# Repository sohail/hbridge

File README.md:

# H Bridge electronic circuit

H-Bridge is an electronic circuit that switches the polarity of voltage applied to a load.

Given the fact that by changing the direction of the rotation the DC motors can run with either polarity. An H bridge is an electronic circuit which can be used to switch the polarity of a attached motor, thus making the motor run forward or in backwards directions.

An H Bridge can be used in many different power electronics. The H Bridge of this repository which is built with few discrete components has one purpose only and that would be to control the direction of the rotation of a brushed DC motor.

### The list of components that you would need to make this circuit

- Two P-channel enhancement mode MOSFETs
- Two NPN BJTs
- Two voltage regulators
- Couple of resistors, to manage the flow of current at the base pins of NPN transistors

### Video of prototype of this circuit

Following is a link of a video about the working prototype of this H-Bridge electronic circuit...

[H-Bridge electronic circuit](https://www.youtube.com/watch?v=_cwA7jFTUsA&t=6s)

### The circuit sketches

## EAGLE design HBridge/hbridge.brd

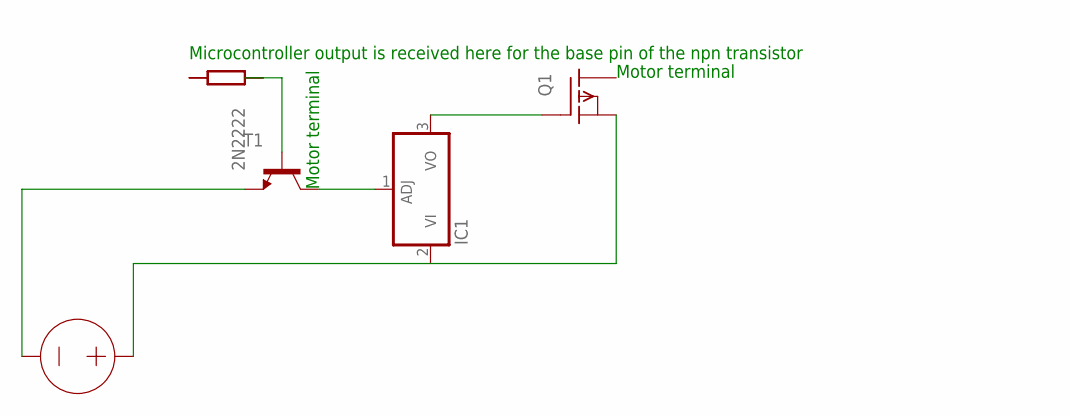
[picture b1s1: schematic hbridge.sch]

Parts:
IC1: 337T; TO220H
Q1: IRF9530; TO220
T1: 2N2222; TO18

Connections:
unnamed: IC1.2 (VI), Q1.3 (S)
unnamed: IC1.3 (VO), Q1.1 (G)
T1_C: IC1.1 (ADJ), T1.3 (C)
T1_E: T1.1 (E)

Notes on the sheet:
Motor terminal
Microcontroller output is received here for the base pin of the npn transistor

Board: 2 copper layers, 3 parts (0 on the bottom side), 3 nets, no tracks yet.

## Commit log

2018-12-21 Update README.md
    Eagle files for an H-Bridge electronic circuit
2018-12-21 Eagle files
2018-12-23 Updating this repository
2018-12-23 Updating README.md
2018-12-23 Updated Eagle files
2018-12-25 Trivial update
